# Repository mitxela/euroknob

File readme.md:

# Eurorack Knob Idea
Hardware and software for the [eurorack knob idea](https://mitxela.com/projects/euroknob)

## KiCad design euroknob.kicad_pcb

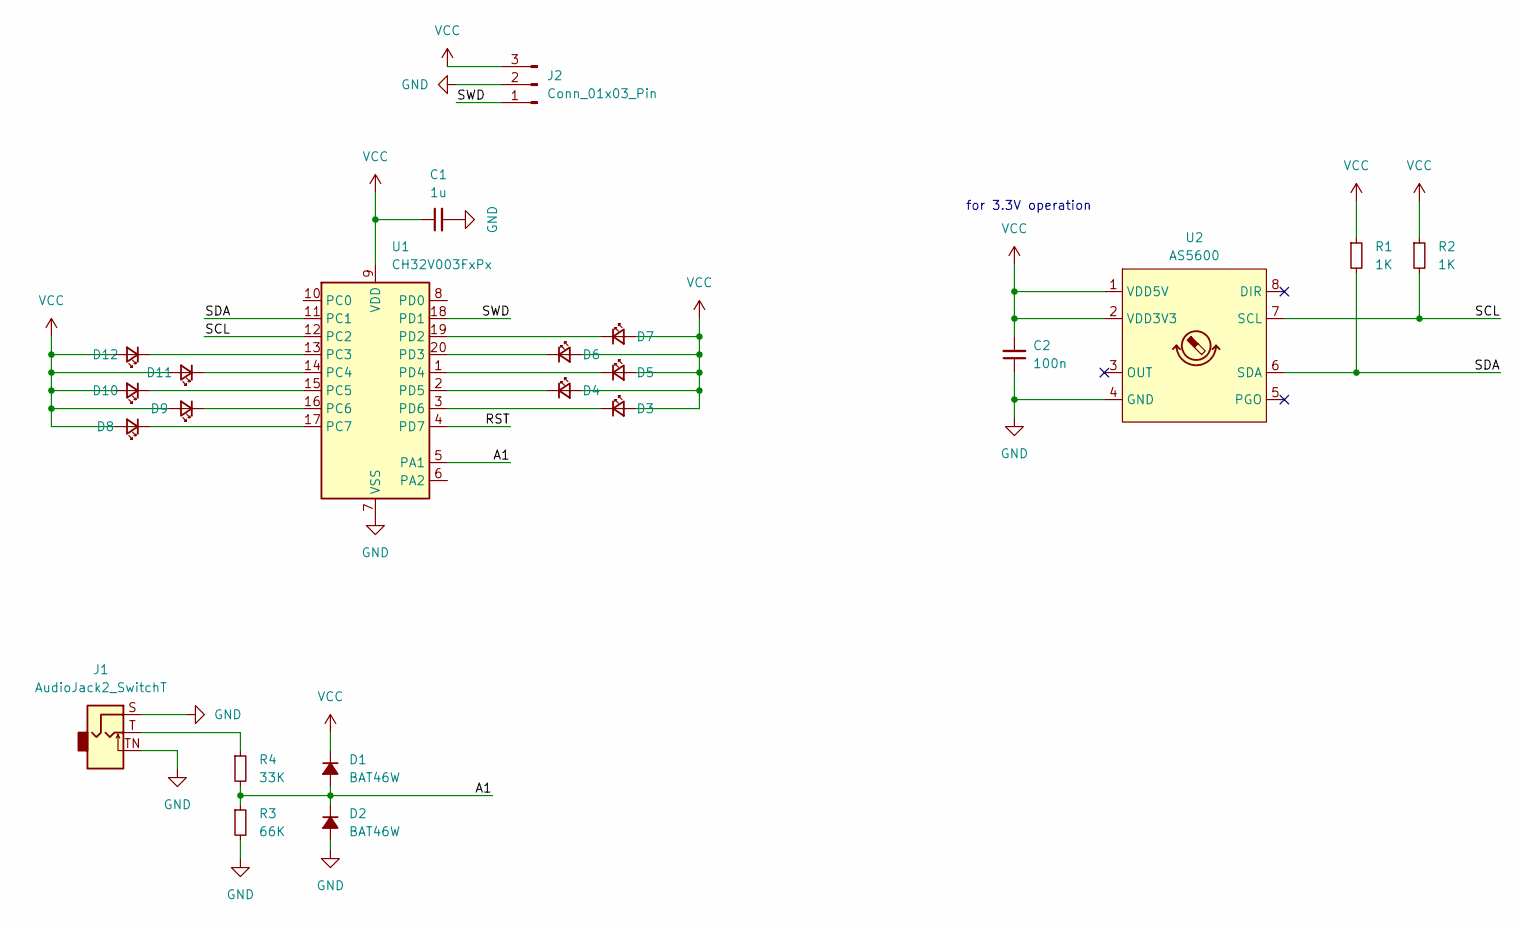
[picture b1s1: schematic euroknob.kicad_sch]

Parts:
C1: 1u; C_0805_2012Metric
C2: 100n; C_0805_2012Metric
D1, D2: BAT46W; Nexperia_CFP3_SOD-123W
D3, D4, D5, D6, D7, D8, D9, D10, D11, D12: LED_Small; LED_0805_2012Metric
J1: AudioJack2_SwitchT; Jack_3.5mm_QingPu_WQP-PJ398SM_Vertical_CircularHoles
J2: Conn_01x03_Pin; PinHeader_1x03_P2.54mm_Vertical
R1, R2: 1K; R_0805_2012Metric
R3: 66K; R_0603_1608Metric
R4: 33K; R_0603_1608Metric
U1: CH32V003FxPx; TSSOP-20_4.4x6.5mm_P0.65mm
U2: AS5600; SOIC-8_3.9x4.9mm_P1.27mm

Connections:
/A1: D1.2 (A), D2.1 (K), R3.1, R4.2, U1.5 (PA1)
/RST: U1.4 (PD7)
/SCL: R2.2, U1.12 (PC2), U2.7 (SCL)
/SDA: R1.2, U1.11 (PC1), U2.6 (SDA)
/SWD: J2.1, U1.18 (PD1)
GND: C1.2, C2.1, D2.2 (A), J1.S, J1.TN, J2.2, R3.2, U1.7 (VSS), U2.4 (GND)
unnamed: D3.1 (K), U1.3 (PD6)
unnamed: D4.1 (K), U1.2 (PD5)
unnamed: D5.1 (K), U1.1 (PD4)
unnamed: D6.1 (K), U1.20 (PD3)
unnamed: D7.1 (K), U1.19 (PD2)
unnamed: D8.1 (K), U1.17 (PC7)
unnamed: D9.1 (K), U1.16 (PC6)
unnamed: D10.1 (K), U1.15 (PC5)
unnamed: D11.1 (K), U1.14 (PC4)
unnamed: D12.1 (K), U1.13 (PC3)
unnamed: J1.T, R4.1
VCC: C1.1, C2.2, D1.1 (K), D3.2 (A), D4.2 (A), D5.2 (A), D6.2 (A), D7.2 (A), D8.2 (A), D9.2 (A), D10.2 (A), D11.2 (A), D12.2 (A), J2.3, R1.1, R2.1, U1.9 (VDD), U2.1 (VDD5V), U2.2 (VDD3V3)

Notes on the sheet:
for 3.3V operation

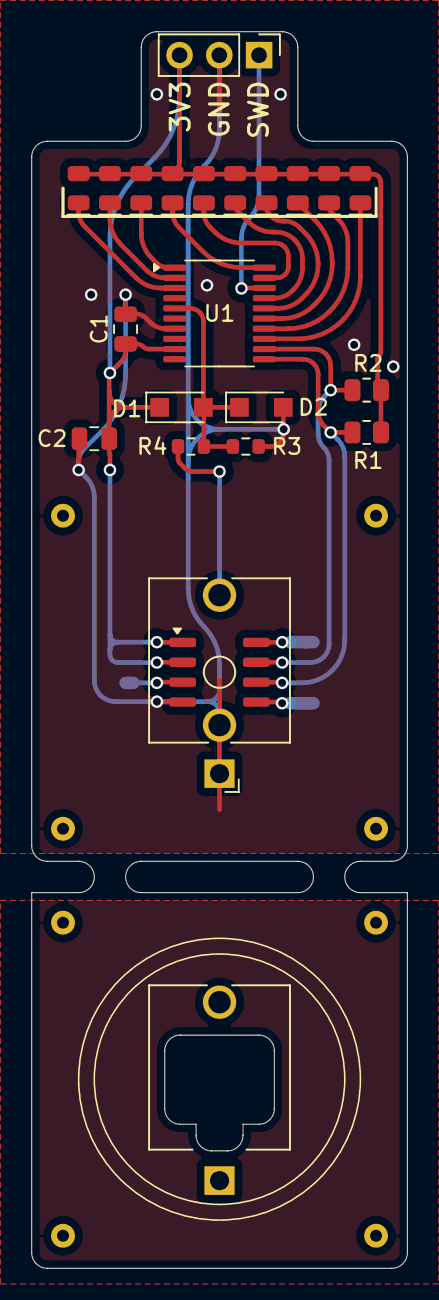
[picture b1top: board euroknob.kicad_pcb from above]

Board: 2 copper layers, 24.0 x 79.0 mm, 23 parts (0 on the bottom side), 17 nets.

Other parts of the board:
JN1: AudioJack2_SwitchT; Jack_3.5mm_QingPu_WQP-PJ398SM_Vertical_CircularHoles

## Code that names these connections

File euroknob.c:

#include "ch32v003fun.h"
#include "lib_i2c.h"
#include <stdio.h>

#define AS5600_ADDR      0x36
#define AS5600_RAW_ANGLE 0x0C
#define AS5600_MAGNITUDE 0x1B

// I2C on PC1,PC2
// ADC PA1
// LEDs on PD6,PD5,PD4,PD3,PD2, PC7,PC6,PC5,PC4,PC3

void init_bargraph()
{
	RCC->APB2PCENR |= RCC_APB2Periph_GPIOC|RCC_APB2Periph_GPIOD;

	GPIOC->CFGLR &= ~((0xf<<(4*7)) | (0xf<<(4*6)) | (0xf<<(4*5)) | (0xf<<(4*4)) | (0xf<<(4*3)));
	GPIOC->CFGLR |=((GPIO_Speed_10MHz | GPIO_CNF_OUT_PP)<<(4*7))
				 | ((GPIO_Speed_10MHz | GPIO_CNF_OUT_PP)<<(4*6))
				 | ((GPIO_Speed_10MHz | GPIO_CNF_OUT_PP)<<(4*5))
				 | ((GPIO_Speed_10MHz | GPIO_CNF_OUT_PP)<<(4*4))
				 | ((GPIO_Speed_10MHz | GPIO_CNF_OUT_PP)<<(4*3));

	GPIOD->CFGLR &= ~((0xf<<(4*6)) | (0xf<<(4*5)) | (0xf<<(4*4)) | (0xf<<(4*3)) | (0xf<<(4*2)));
	GPIOD->CFGLR |=((GPIO_Speed_10MHz | GPIO_CNF_OUT_PP)<<(4*6))
				 | ((GPIO_Speed_10MHz | GPIO_CNF_OUT_PP)<<(4*5))
				 | ((GPIO_Speed_10MHz | GPIO_CNF_OUT_PP)<<(4*4))
				 | ((GPIO_Speed_10MHz | GPIO_CNF_OUT_PP)<<(4*3))
				 | ((GPIO_Speed_10MHz | GPIO_CNF_OUT_PP)<<(4*2));

	GPIOD->OUTDR |= 0xFF;
	GPIOC->OUTDR |= 0xFF;
}

void draw_bargraph(uint16_t v)
{
	uint8_t outD = 0xFF, outC=0xFF;
	if (v > 205) outD &=~(1<<6);
	if (v > 614) outD &=~(1<<5);
	if (v >1024) outD &=~(1<<4);
	if (v >1433) outD &=~(1<<3);
	if (v >1842) outD &=~(1<<2);
	if (v >2252) outC &=~(1<<7);
	if (v >2662) outC &=~(1<<6);
	if (v >3071) outC &=~(1<<5);
	if (v >3481) outC &=~(1<<4);
	if (v >3890) outC &=~(1<<3);

	GPIOD->OUTDR = outD;
	GPIOC->OUTDR = outC;
	Delay_Us(50);
	GPIOD->OUTDR |= 0xFF;
	GPIOC->OUTDR |= 0xFF;
}

void init_adc()
{
	RCC->APB2PCENR |= RCC_APB2Periph_GPIOA | RCC_APB2Periph_ADC1;

	// PA1 is analog input chl 1
	GPIOA->CFGLR &= ~(0xf<<(4*1));	// CNF = 00: Analog, MODE = 00: Input

	RCC->APB2PRSTR |= RCC_APB2Periph_ADC1;
	RCC->APB2PRSTR &= ~RCC_APB2Periph_ADC1;

	RCC->CFGR0 &= ~(0x1F<<11); //RCC_ADCPRE = 0
	ADC1->RSQR1 = 0;
	ADC1->RSQR2 = 0;
	ADC1->RSQR3 = 1;
	// sampling time
	ADC1->SAMPTR2 &= ~(ADC_SMP0<<(3*7));
	ADC1->SAMPTR2 |= 7<<(3*7);

	// turn on, set sw trig
	ADC1->CTLR2 |= ADC_ADON | ADC_EXTSEL;
	// reset calibration
	ADC1->CTLR2 |= ADC_RSTCAL;
	while(ADC1->CTLR2 & ADC_RSTCAL);
	// calibrate
	ADC1->CTLR2 |= ADC_CAL;
	while(ADC1->CTLR2 & ADC_CAL);
}

uint16_t read_adc(void)
{
	ADC1->CTLR2 |= ADC_SWSTART;
	while(!(ADC1->STATR & ADC_EOC));
	return ADC1->RDATAR;
}

int main()
{
	SystemInit();

	init_bargraph();
	init_adc();

	if (i2c_init(I2C_CLK_100KHZ) != I2C_OK) printf("Failed to init I2C");
	Delay_Ms(100);

	while(1){
		uint8_t buf[2];
		uint16_t raw_angle=0, magnitude=0;

		if (i2c_read(AS5600_ADDR, AS5600_RAW_ANGLE, buf, 2) == I2C_OK)
			raw_angle = (buf[0]<<8)+ buf[1];

		if (i2c_read(AS5600_ADDR, AS5600_MAGNITUDE, buf, 2) == I2C_OK)
			magnitude = (buf[0]<<8)+ buf[1];

		uint16_t raw_adc = read_adc();

		if (magnitude > 500) { // magnitude is about 2000 when plugged in
			draw_bargraph(raw_angle);
		} else {
			draw_bargraph(raw_adc*4);
		}
		//printf("Read %04d / %04d / %04d \n", raw_angle, magnitude, raw_adc);

		Delay_Ms(10);
	}

/*
*/

}

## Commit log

2025-02-17 read out AS5600 angle and magnitude
2025-02-18 initial pcb layout
2025-02-18 rounding
2025-04-09 draw bargraph
2025-04-10 read ADC input too
2025-04-24 readme
